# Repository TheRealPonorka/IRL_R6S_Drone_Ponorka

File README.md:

# Tom Clancy's Rainbow Six: Siege - Recon Drone by Ponorka
Last update: 22/09/2026

This project is inspired by a fictional tool called Recon drone from game Tom Clancy's Rainbow Six: Siege.
I have created a fan page on facebook for this project, where I will post some updates while I am working on it or doing some stuffs with it, here:
https://www.facebook.com/profile.php?id=61594372602997

I have built a similar drone, which was based on another github project https://github.com/hemrobotics/recon-drone and I was wondering: "Can this drone be really a fully operational 2 wheeled remote controlled drone?" This github repo should be the answer for this.

# WIP - Work In Progress
This repo is still in progress. Right now 22/09/2026 the PCB is ready and I am waiting for the supplies so I can build the prototype.
The firmware is mostly ready, but it needs polishing.
Unfortunately, my experience in coding other than PowerShell is HIGHLY LIMITED, so I apologize from everyone who might check the code and see what is happening there :D
So a lot of AI coding will be involved in this project. Sorry to everyone, I am just an enthusiast gamer in this case. In my professional life I am a SysAdmin :D

Slowly but there will be updates here to add the details about this project.

# Make it but don't sell it!
Keep in mind that this is a hobby project and I am giving it available to everyone, who is interested to build this project. So far I am not planning to make money from this and I would be happy to keep this mindset in a same way for everyone.
Don't make a hustle from this project! If you are interested, but you can't build it by yourself, ask someone, give the person all the necessary HW and pay him for the worktime, but do not sell it for profit!
I have applied proper licensing description for this reason.
If you will assemble it, credit my github/facebook fan page properly so others can reach this project as well :)
Thanks for understanding.

# Now the "FUN" Part
Okay, so if you came to this place, you probably want to build your own Recon drone (or maybe just get an inspiration, I don't know, I can't read minds :D ).
I will do my best to explain everything around so the build would be easier to complete for anyone :)

The schematics and Parts
Took me some time to get back to this knowledge, as I did not work on any electronics for several years. I figured out some basic stuffs, which were needed in addition to properly have all the stuffs working together.
As I wanted to add all the possible features what a recon drone have in R6S, I needed think over, what I want to achieve:
1. Self-balancing 2 wheeled robot
2. Camera for reconnaissance
3. LED Spotlight to light up darker places
4. Addressable RGB LED strip with 6 LEDs to replicate the visuals of the drone
5. Operate the entire drone from a single 18650 Li-Po battery cell.
6. Microphone to hear via the web stream what is happening arround. (Unfortunately could not achieve this, so I dropped this feature)

So, how to achieve that?
First we need a microcontroller (MCU) robust enough to handle all the stuffs. After reviewing all the possibilities and cost effectiveness, I decided to go with ESP32-S3 CAM DEVKITC especially from GOOUUU.
For now this is sufficient for everything we need (later on I might rethink the schematics and PCB layout with fully self-built PCB using only the MCU and not the devkit).
For camera module I decided to go with OV3660, as this module has good enough resolution, while keeping the FPS high enough to have a smooth experience.
Early build I planned with omnidirectional microphone module as well, however after further testing this came out as unusable for real time audio stream so I left this idea out of the final build.
The motors I have selected are N20 small geared motors operating on 6V with gear reduction 1:30 and built-in HAL encoder. This gives the drone possibly enough torque and power to balance, while keeping the voltage on lower side (more on it later)
The motor driver is a DRV8833, there is not much to talk about it, it is a sweet spot for this build. Low cost, low power.
The balancing is solved by IMU module BMI270, slotted on the main board.
Now here comes the power consumption part. In my previous attempt to build this drone I was happy to handle everything with only one 18650 LiPo battery cell and I wanted to keep it that way.
I have found a 18650 battery cell shield, which can handle massive current delivery at 5V (up to 3A): https://www.aliexpress.com/item/1005006252337213.html
With this solution I can easily power the ESP32, the LED strip, the motor drivers and the HAL sensors. It might not be able to run for tens of hours, but this solution should be sufficient to handle power delivery for several hours.
The battery shield needed some modifications:
- removed USB-A port
- Removed USB-C charging port and soldered cables for external USB-C connector. This was necessary to add the USB-C charging port on the back of the drone, next to the ON/OFF switch and Wi-Fi antenna.
And if you have a spare 18650 battery cell, you can replace it whenever you need inside chasis. Even though I do not recommend it, as replacement of the battery needs quite some screws to remove. This is something I did not solve in easier way yet.
There was a need to lower voltage from the motors HAL sensors. As they are operating on 5V from the battery shield, but this voltage would fry the MCU, as the MCU operates the GPIO pins with 3.3V. I needed to add a 4-channel bi-polar level shifter, so we don't fry our MCU with 5V input :)

The PCB
After several iterations of how and where the parts should be placed, I finished with this version of 2-layer PCB. The entire PCB size is 45x99.2 mm.

Already ordered PCB from manufacturer

3D overview of the final board

# The Code
This is where my knowledge is really behind, and if you will review my code later on, you might find a lot of issues with that.
The entire firmware code is based on vide coding in cooperation with Cursor. At the beginning I used Claude Sonnet 4, then I changed it to Cursor Grok 4.6
Right now, the firmware is functioning with these features on test breadboard:
- LED strip is creating the animation of the 6 ARGB LEDs based on the calculation from recorded footage of 30ms from middle to outside and back, default color is GREEN.
- Spotlight high brightness single white LED can be toggled ON/OFF
- Motors are spinning
- IMU is correctly communicating with MCU and based on the tilt it is regulating the motor movement
- MCU Wi-Fi module is correctly generating AP with SSID: "R6_Recone_Drone" and WPA password: "ReconDrone123"
- A basic (so far not modified) webserver is generated by the MCU on IP 192.168.4.1 with camera stream and buttons to operate the drone (move, LED strip color change, LED spotlight toggle, IMU data)

# The Body
I took screenshots from the game and based on it I tried to model out the outside of the drone as accurate as I could.
The body is created from 4 parts:
- TOP
- BOTTOM
- RIGH and LEFT motor/wheel holder
IT IS NOT PERFECTLY ACCURATE.
There were some challenges which I had to solve during initial test prints so it could be printed easier on 3D printer and assemble at the end.
From the front part it looks almost identical to one in the game, however the back I had to change a bit.
The top part on the back is stripped a bit, which I added for the bottom. The reason is to assemble easier the insides: USB-C charging port, Wi-Fi antenna and ON/OFF switch together with the electronics boards inside.

The motors I used are the following: https://www.aliexpress.com/item/1005012449655687.html with these specifications selected: "1 to 30, DC 6V A06 Type" and they are screwed in with really small 1.6mm screws
I have created an overengineered stand for this, you can see it on the pictures and the model.

# The test
I know, the breadboard "spaghetti" looks terrifying, but if you follow the schematics, you don't need to be afraid of it :) It is easier than you think!
Anyway, after many attempts, I have finally reached the testing state, where I can (hopefully) confidently say: IT WORKS!

# Next steps
Currently I am waiting for my final PCB (this is my 4th attempt, so my 4th order. I know I f-ed up. I did not start with breadboard testing before I ordered previous PCB attemtps) I have ordered, based on the gerber file you can find in "SchematicsAndPCB"

Hopefully, once it will arrive and solder all the components (Bill of materials, a.k.a. BOM you can find in "SchematicsAndPCB") it will finally work. Previous (3rd) version was already working, but I connected one motor signal to a PIN, which is used for Wi-Fi, so I had to redo the pinouts a bit.

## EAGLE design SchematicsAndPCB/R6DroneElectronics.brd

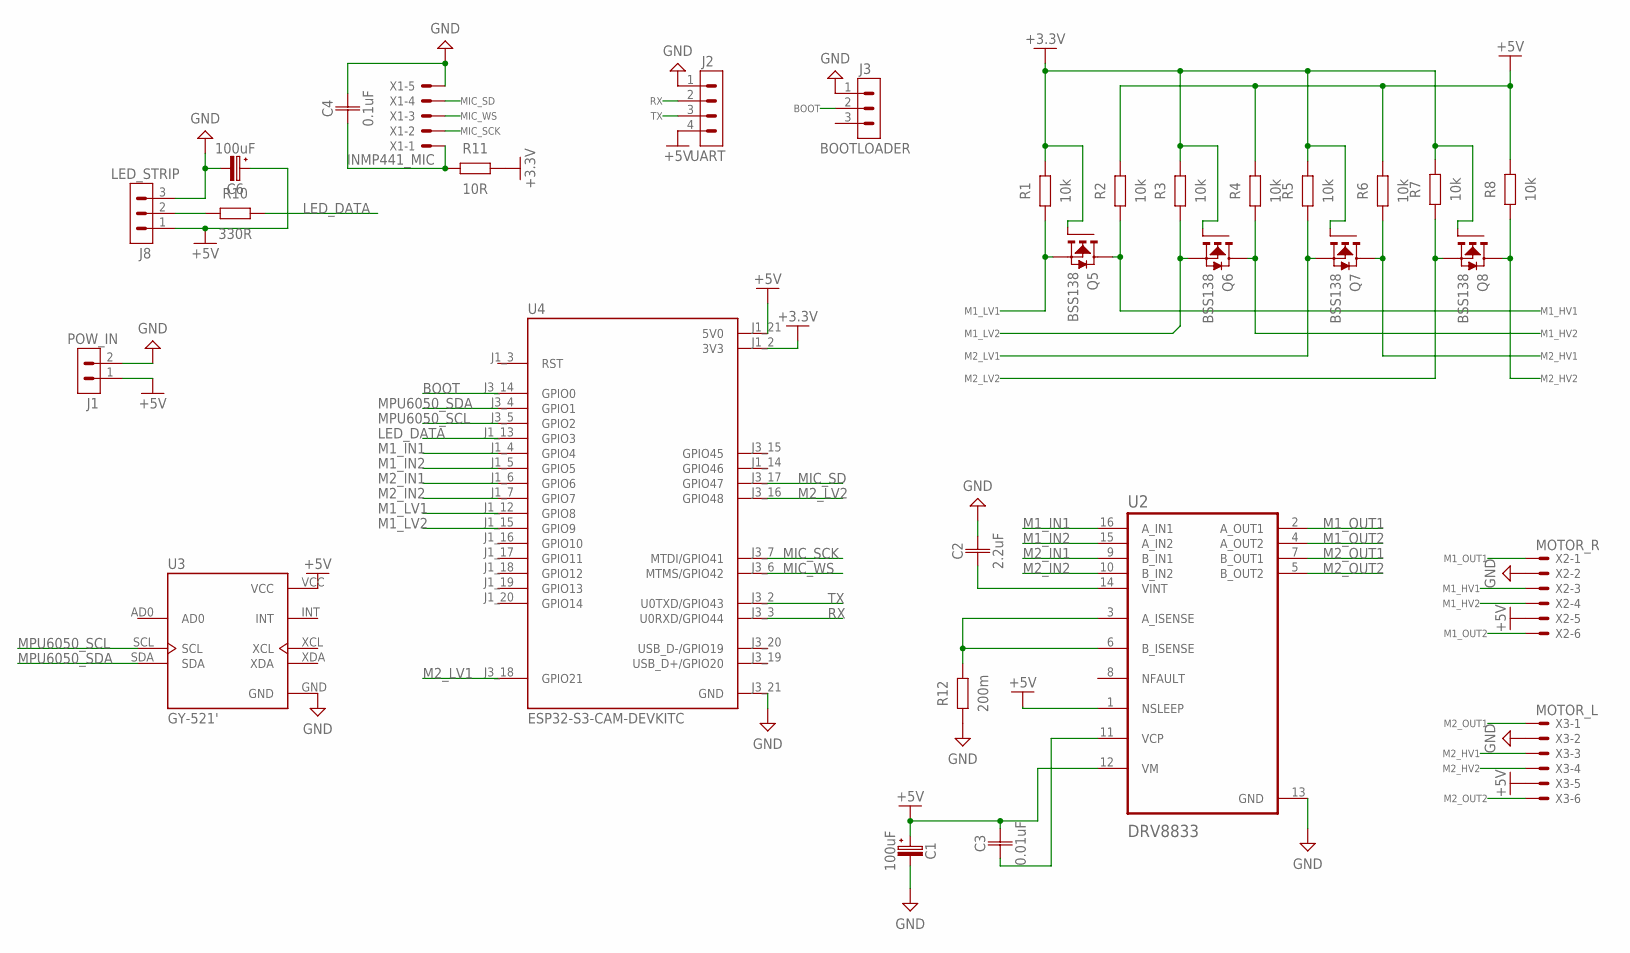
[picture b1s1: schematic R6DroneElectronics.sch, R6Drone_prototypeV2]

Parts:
C1, C6: 100uF; CAPAE1030X1050N
C2: 2.2uF; CAPC4532X135
C3: 0.01uF; CAPC4532X135
C4: 0.1uF; CAPC4532X135
J1: POW_IN; B2B-XH-A
J2: UART; B4B-XH-A
J3: BOOTLOADER; B3B-XH-A
J8: LED_STRIP; B3B-XH-A
Q5, Q6, Q7, Q8: BSS138; SOT23
R1, R2, R3, R4, R5, R6, R7, R8: 10k; RESC3224X71
R10: 330R; RESC3224X71
R11: 10R; RESC3224X71
R12: 200m; RESC3224X71
U2: DRV8833; SOP65P640X120-16N
U3: GY-521'; MODULE_GY-521
U4: ESP32-S3-CAM-DEVKITC
X1: INMP441_MIC; JST-XH-05-PACKAGE-LONG-PAD
X2: MOTOR_R; JST-XH-06-PACKAGE-LONG-PAD
X3: MOTOR_L; JST-XH-06-PACKAGE-LONG-PAD

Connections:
+3.3V: Q5.1 (G), Q6.1 (G), Q7.1 (G), Q8.1 (G), R1.2, R3.2, R5.2, R7.2, R11.2, U4.J1_2 (3V3)
+5V: C1.1 (+), C3.2, C6.1 (+), J1.1, J2.4, J8.1, R2.2, R4.2, R6.2, R8.2, U2.1 (NSLEEP), U2.12 (VM), U3.VCC, U4.J1_21 (5V0), X2.5, X3.5
BOOT: J3.2, U4.J3_14 (GPIO0)
GND: C1.2 (-), C2.2, C4.2, C6.2 (-), J1.2, J2.1, J3.1, J8.3, R12.1, U2.13 (GND), U3.GND, U4.J3_21 (GND), X1.5, X2.2, X3.2
LED_DATA: R10.2, U4.J1_13 (GPIO3)
M1_HV1: Q5.3 (D), R2.1, X2.3
M1_HV2: Q6.3 (D), R4.1, X2.4
M1_IN1: U2.16 (A_IN1), U4.J1_4 (GPIO4)
M1_IN2: U2.15 (A_IN2), U4.J1_5 (GPIO5)
M1_LV1: Q5.2 (S), R1.1, U4.J1_12 (GPIO8)
M1_LV2: Q6.2 (S), R3.1, U4.J1_15 (GPIO9)
M1_OUT1: U2.2 (A_OUT1), X2.1
M1_OUT2: U2.4 (A_OUT2), X2.6
M2_HV1: Q7.3 (D), R6.1, X3.3
M2_HV2: Q8.3 (D), R8.1, X3.4
M2_IN1: U2.9 (B_IN1), U4.J1_6 (GPIO6)
M2_IN2: U2.10 (B_IN2), U4.J1_7 (GPIO7)
M2_LV1: Q7.2 (S), R5.1, U4.J3_18 (GPIO21)
M2_LV2: Q8.2 (S), R7.1, U4.J3_16 (GPIO48)
M2_OUT1: U2.7 (B_OUT1), X3.1
M2_OUT2: U2.5 (B_OUT2), X3.6
MIC_SCK: U4.J3_7 (MTDI/GPIO41), X1.2
MIC_SD: U4.J3_17 (GPIO47), X1.4
MIC_WS: U4.J3_6 (MTMS/GPIO42), X1.3
MPU6050_SCL: U3.SCL, U4.J3_5 (GPIO2)
MPU6050_SDA: U3.SDA, U4.J3_4 (GPIO1)
unnamed: J8.2, R10.1
unnamed: C2.1, U2.14 (VINT)
unnamed: R12.2, U2.3 (A_ISENSE), U2.6 (B_ISENSE)
unnamed: C3.1, U2.11 (VCP)
unnamed: C4.1, R11.1, X1.1
RX: J2.2, U4.J3_3 (U0RXD/GPIO44)
TX: J2.3, U4.J3_2 (U0TXD/GPIO43)

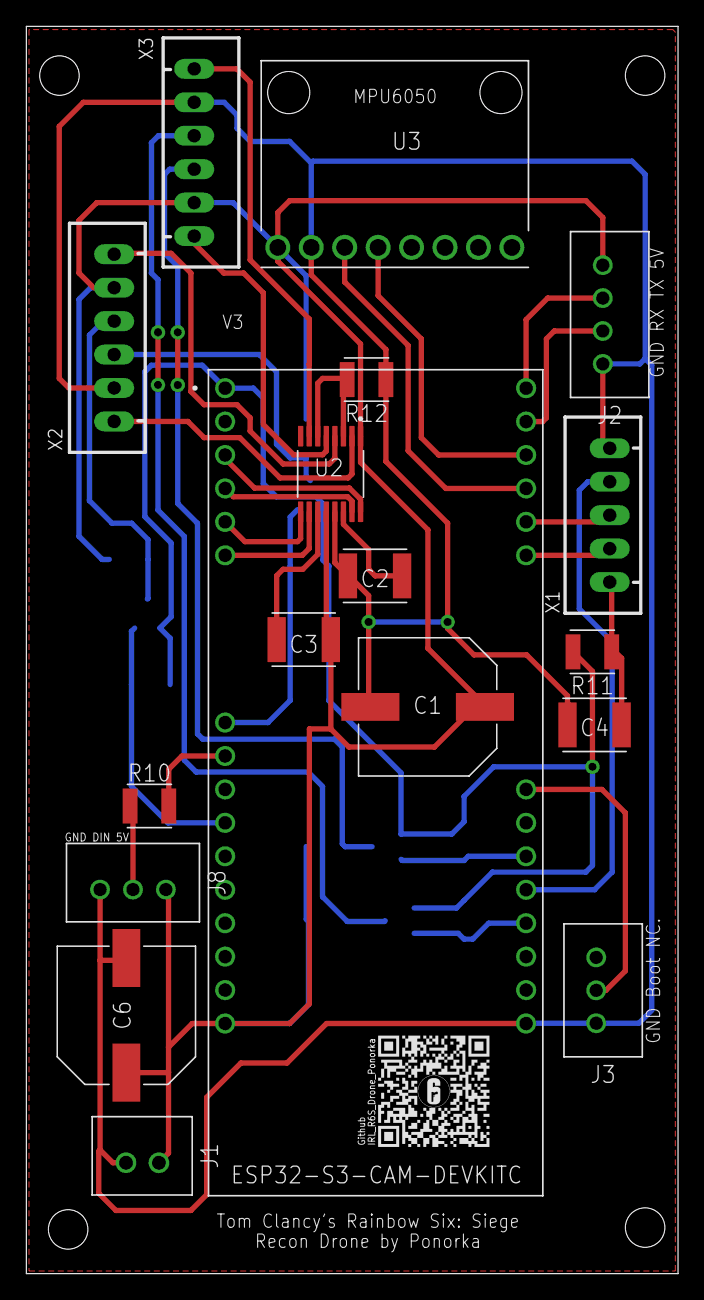
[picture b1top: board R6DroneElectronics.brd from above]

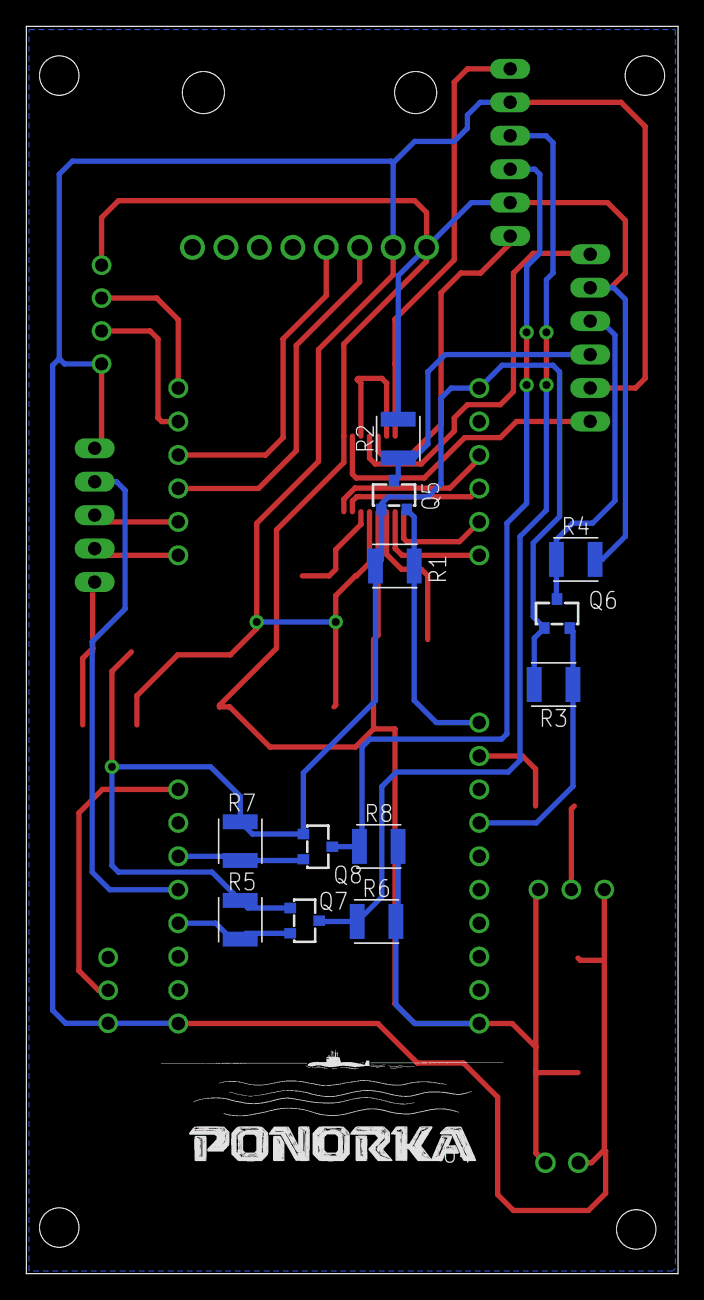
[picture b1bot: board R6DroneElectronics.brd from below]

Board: 2 copper layers, 49.5 x 94.7 mm, 30 parts (12 on the bottom side), 33 nets.

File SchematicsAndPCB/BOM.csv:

Reference Designators;Quantity;Description;Package;Value;Manufacturer;Manufacturer Part Number;Vendor;Vendor Part Number;Top/Bottom
U1;1;IMU;1line 7-pin daughter board;BMI270;https://www.aliexpress.com/item/1005012475229129.htm;;;;Top
C1;1;Capacitor Polarised - Generic;CAPAE1030X1050N;100uF;;;;;Top
C2;1;Capacitor - Generic;CAPC4532X135;2.2uF;;;;;Top
C3;1;Capacitor - Generic;CAPC4532X135;0.01uF;;;;;Top
U2;1;Motor driver;HTSSOP16;DRV8833PWP;Texas Instruments;;;;Top
LED_STRIP;1;JST XH Connector 2 Pin;JST-XH-03-PACKAGE-LONG-PAD;;;;;;Top
LED_W;1;JST XH Connector 2 Pin;JST-XH-02-PACKAGE-LONG-PAD;;;;;;Top
POW_IN;1;JST XH Connector 2 Pin;JST-XH-02-PACKAGE-LONG-PAD;;;;;;Top
M1_RIGHT, M2_LEFT;2;JST XH Connector 6 Pin;JST-XH-06-PACKAGE-LONG-PAD;;;;;;Top
U3;1;MCU;2 line 40-pin devkit board;GOOUUU-ESP32-S3-CAM-DEVKITC;https://www.aliexpress.com/item/1005008568072063.html;;;;Top
Q1;1;NPN Transistor - Popular parts;SOT95P237X112-3N;MMBT3904;;MMBT3904-7-F;;;Top
Q5, Q6, Q7, Q8;4;N-Channel MOSFET - Popular parts;SOT23;BSS138;;;;;Bottom
R1, R2, R3, R4, R5, R6, R7, R8;8;Resistor Fixed - Generic;RESC3224X71;10k;;;;;Bottom
R9;1;Resistor Fixed - Generic;RESC3224X71;62R;;;;;Top
R10;1;Resistor Fixed - Generic;RESC3224X71;330R;;;;;Top
R12;1;Resistor Fixed - Generic;RESC3224X71;1k;;;;;Top
